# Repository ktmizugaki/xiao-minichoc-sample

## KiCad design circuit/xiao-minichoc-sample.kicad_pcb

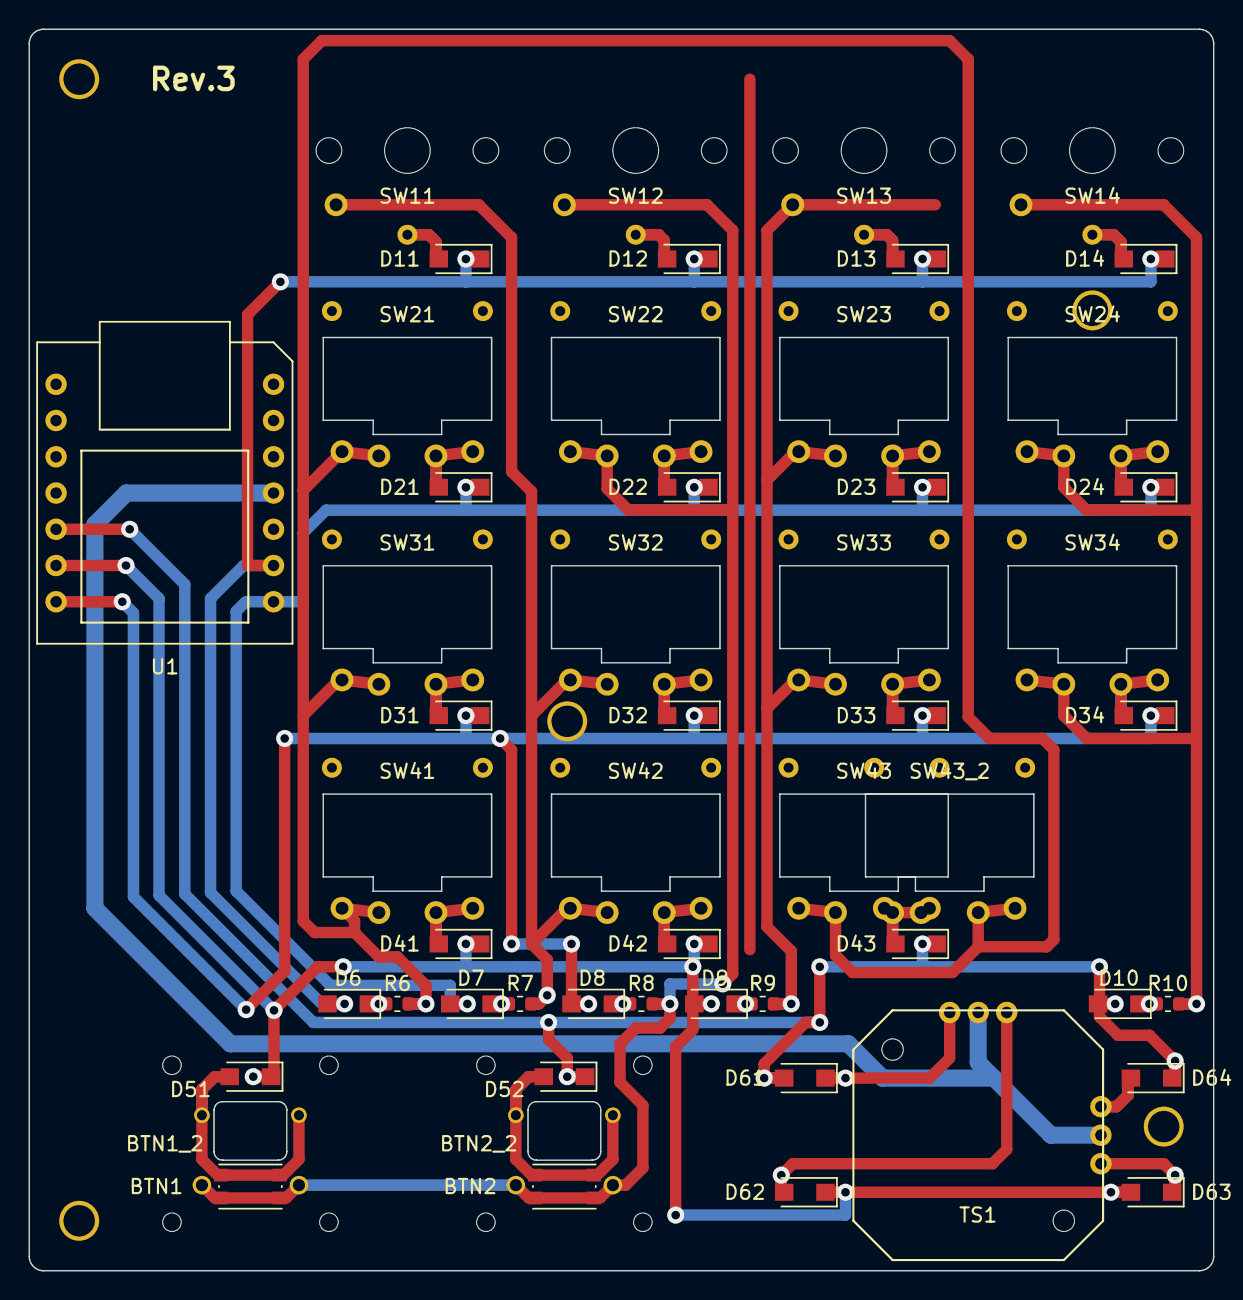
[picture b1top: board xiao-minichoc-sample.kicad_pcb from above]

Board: 2 copper layers, 83.0 x 87.0 mm, 58 parts (0 on the bottom side), 37 nets.

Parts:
BTN1: BUTTON1; SW_SPST_KMR2
BTN1_2: BUTTON1; Kailh_X_Switch_PG1425_Reversible
BTN2: BUTTON2; SW_SPST_KMR2
BTN2_2: BUTTON2; Kailh_X_Switch_PG1425_Reversible
D6, D7, D8, D9, D10: 1SS355VM; D_SOD-123-323_Reversible
D11, D12, D13, D14, D21, D22, D23, D24, D31, D32, D33, D34, D41, D42, D43, D51, D52: 1N4148W; D_SOD-123-323_Reversible
D61, D62, D63, D64: SS2040FL; D_SOD-123-323_Reversible
Hole1: Hole1; MountingHole_2.2mm_M2_Pad
Hole2: Hole2; MountingHole_2.2mm_M2_Pad
Hole3: Hole3; MountingHole_2.2mm_M2_Pad
Hole4, Hole4#2: Hole4; MountingHole_2.2mm_M2_Pad
R6, R7, R8, R9, R10: ~~600; R_0603_1608Metric_Reversible
SW11: SW11; Kailh_Choc_V1_PG1350_Reversible
SW12: SW12; Kailh_Choc_V1_PG1350_Reversible
SW13: SW13; Kailh_Choc_V1_PG1350_Reversible
SW14: SW14; Kailh_Choc_V1_PG1350_Reversible
SW21: SW21; Kailh_Choc_Mini_PG1232_Reversible
SW22: SW22; Kailh_Choc_Mini_PG1232_Reversible
SW23: SW23; Kailh_Choc_Mini_PG1232_Reversible
SW24: SW24; Kailh_Choc_Mini_PG1232_Reversible
SW31: SW31; Kailh_Choc_Mini_PG1232_Reversible
SW32: SW32; Kailh_Choc_Mini_PG1232_Reversible
SW33: SW33; Kailh_Choc_Mini_PG1232_Reversible
SW34: SW34; Kailh_Choc_Mini_PG1232_Reversible
SW41: SW41; Kailh_Choc_Mini_PG1232_Reversible
SW42: SW42; Kailh_Choc_Mini_PG1232_Reversible
SW43, SW43_2: SW43; Kailh_Choc_Mini_PG1232_Reversible
TS1: JT8P-3.2T-B10K-1-16Y-2; JT8P-3.2T-B10K-1-16Y
U1: SeeeduinoXIAO; Seeeduino_XIAO_THT_UpsideDown

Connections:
/A0: TS1.x2, TS1.y2, U1.4
/D6: D6.2, D11.1, D12.1, D13.1, D14.1, U1.6
/D7: D7.2, D21.1, D22.1, D23.1, D24.1, U1.7
/D8: D8.2, D31.1, D32.1, D33.1, D34.1, Hole4#2.1, U1.8
/D9: D9.2, D41.1, D42.1, D51.1, D62.1, D63.2, U1.9
/D10: D10.2, D43.1, D52.1, D61.2, D64.1, U1.10
/RD6: R6.2, SW21.1, SW31.1, SW41.1, SW43.1, SW43_2.2
/RD7: R7.2, SW11.2, SW32.1, SW42.1
/RD8: BTN1.1, BTN1_2.1, BTN2.1, BTN2_2.1, R8.2, SW12.2, SW22.1
/RD9: R9.2, SW13.2, SW23.1, SW33.1
/RD10: R10.2, SW14.2, SW24.1, SW34.1
unnamed: BTN1.2, BTN1_2.2, D51.2
unnamed: BTN2.2, BTN2_2.2, D52.2
unnamed: D6.1, R6.1
unnamed: D7.1, R7.1
unnamed: D8.1, R8.1
unnamed: D9.1, R9.1
unnamed: D10.1, R10.1
unnamed: D11.2, SW11.1
unnamed: D12.2, SW12.1
unnamed: D13.2, SW13.1
unnamed: D14.2, SW14.1
unnamed: D21.2, SW21.2
unnamed: D22.2, SW22.2
unnamed: D23.2, SW23.2
unnamed: D24.2, SW24.2
unnamed: D31.2, SW31.2
unnamed: D32.2, SW32.2
unnamed: D33.2, SW33.2
unnamed: D34.2, SW34.2
unnamed: D41.2, SW41.2
unnamed: D42.2, SW42.2
unnamed: D43.2, SW43.2, SW43_2.1
unnamed: D61.1, TS1.x3
unnamed: D62.2, TS1.x1
unnamed: D63.1, TS1.y1
unnamed: D64.2, TS1.y3

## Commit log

2022-06-24 Fix ocational mouse cursor jump
2022-06-24 Add KeyboardLibrary
2022-06-24 Add MeasureDiode
2022-06-24 Add png version of schematic
2022-09-29 Update keyboard library
2022-10-10 Rework firmware
    - Restructure sources
    - Refine analog handling
    - Support layer
2022-10-22 Fix analog handling
2022-10-23 Fix mask operation
